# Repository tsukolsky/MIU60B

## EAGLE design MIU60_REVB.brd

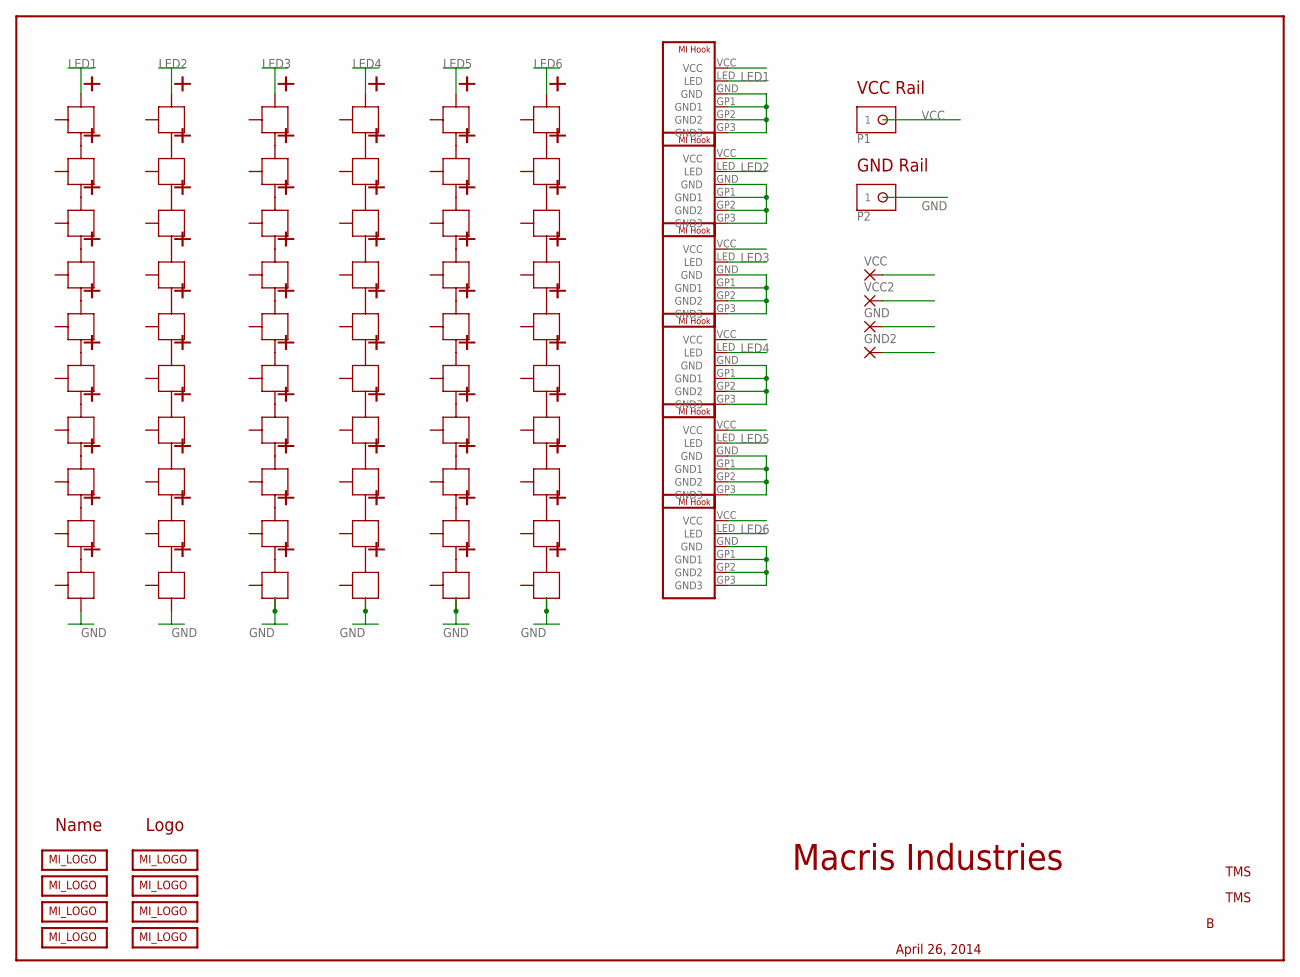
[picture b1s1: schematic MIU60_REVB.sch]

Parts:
GND, GND2: SMD5; SMD2,54-5,08
P1, P2: PAD-10G; PAD_10G
U$1, U$3, U$5, U$6: MI_LOGO-50MIL; MI_LOGO_NAME_2
U$2, U$4, U$7, U$8: MI_LOGO-2014_USA; MACRIS_USA_LOGO
U$9, U$10, U$11, U$12, U$13, U$14: MI_DRIVER_HOOKUP; MI_DRIVE_HOOKUP
U$16, U$17, U$18, U$19, U$20, U$21, U$22, U$23, U$24, U$25, U$26, U$27, U$28, U$29, U$30, U$31, U$32, U$33, U$34, U$35, U$36, U$37, U$38, U$39, U$40, U$41, U$42, U$43, U$44, U$45, U$46, U$47, U$48, U$49, U$50, U$51, U$52, U$53, U$54, U$55, U$56, U$57, U$58, U$59, U$60, U$61, U$62, U$63, U$64, U$65, U$66, U$67, U$68, U$69, U$70, U$71, U$72, U$73, U$74, U$75: CREE_XP; XP
VCC, VCC2: SMD5; SMD2,54-5,08

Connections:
GND: GND.1, GND2.1, P2.1, U$9.GND, U$9.GP1 (GND1), U$9.GP2 (GND2), U$9.GP3 (GND3), U$10.GND, U$10.GP1 (GND1), U$10.GP2 (GND2), U$10.GP3 (GND3), U$11.GND, U$11.GP1 (GND1), U$11.GP2 (GND2), U$11.GP3 (GND3), U$12.GND, U$12.GP1 (GND1), U$12.GP2 (GND2), U$12.GP3 (GND3), U$13.GND, U$13.GP1 (GND1), U$13.GP2 (GND2), U$13.GP3 (GND3), U$14.GND, U$14.GP1 (GND1), U$14.GP2 (GND2), U$14.GP3 (GND3), U$25.NEGATIVE, U$25.NEGATIVE1 (NEGATIVE), U$35.NEGATIVE, U$35.NEGATIVE1 (NEGATIVE), U$45.NEGATIVE, U$45.NEGATIVE1 (NEGATIVE), U$55.NEGATIVE, U$55.NEGATIVE1 (NEGATIVE), U$65.NEGATIVE, U$65.NEGATIVE1 (NEGATIVE), U$75.NEGATIVE, U$75.NEGATIVE1 (NEGATIVE)
LED1: U$9.LED, U$16.POSITIVE, U$16.POSITIVE1 (POSITIVE)
LED2: U$10.LED, U$26.POSITIVE, U$26.POSITIVE1 (POSITIVE)
LED3: U$11.LED, U$36.POSITIVE, U$36.POSITIVE1 (POSITIVE)
LED4: U$12.LED, U$46.POSITIVE, U$46.POSITIVE1 (POSITIVE)
LED5: U$13.LED, U$56.POSITIVE, U$56.POSITIVE1 (POSITIVE)
LED6: U$14.LED, U$66.POSITIVE, U$66.POSITIVE1 (POSITIVE)
unnamed: U$16.NEGATIVE, U$16.NEGATIVE1 (NEGATIVE), U$17.POSITIVE, U$17.POSITIVE1 (POSITIVE)
unnamed: U$17.NEGATIVE, U$17.NEGATIVE1 (NEGATIVE), U$18.POSITIVE, U$18.POSITIVE1 (POSITIVE)
unnamed: U$18.NEGATIVE, U$18.NEGATIVE1 (NEGATIVE), U$19.POSITIVE, U$19.POSITIVE1 (POSITIVE)
unnamed: U$19.NEGATIVE, U$19.NEGATIVE1 (NEGATIVE), U$20.POSITIVE, U$20.POSITIVE1 (POSITIVE)
unnamed: U$20.NEGATIVE, U$20.NEGATIVE1 (NEGATIVE), U$21.POSITIVE, U$21.POSITIVE1 (POSITIVE)
unnamed: U$21.NEGATIVE, U$21.NEGATIVE1 (NEGATIVE), U$22.POSITIVE, U$22.POSITIVE1 (POSITIVE)
unnamed: U$22.NEGATIVE, U$22.NEGATIVE1 (NEGATIVE), U$23.POSITIVE, U$23.POSITIVE1 (POSITIVE)
unnamed: U$23.NEGATIVE, U$23.NEGATIVE1 (NEGATIVE), U$24.POSITIVE, U$24.POSITIVE1 (POSITIVE)
unnamed: U$24.NEGATIVE, U$24.NEGATIVE1 (NEGATIVE), U$25.POSITIVE, U$25.POSITIVE1 (POSITIVE)
unnamed: U$56.NEGATIVE, U$56.NEGATIVE1 (NEGATIVE), U$57.POSITIVE, U$57.POSITIVE1 (POSITIVE)
unnamed: U$57.NEGATIVE, U$57.NEGATIVE1 (NEGATIVE), U$58.POSITIVE, U$58.POSITIVE1 (POSITIVE)
unnamed: U$26.NEGATIVE, U$26.NEGATIVE1 (NEGATIVE), U$27.POSITIVE, U$27.POSITIVE1 (POSITIVE)
unnamed: U$27.NEGATIVE, U$27.NEGATIVE1 (NEGATIVE), U$28.POSITIVE, U$28.POSITIVE1 (POSITIVE)
unnamed: U$28.NEGATIVE, U$28.NEGATIVE1 (NEGATIVE), U$29.POSITIVE, U$29.POSITIVE1 (POSITIVE)
unnamed: U$29.NEGATIVE, U$29.NEGATIVE1 (NEGATIVE), U$30.POSITIVE, U$30.POSITIVE1 (POSITIVE)
unnamed: U$30.NEGATIVE, U$30.NEGATIVE1 (NEGATIVE), U$31.POSITIVE, U$31.POSITIVE1 (POSITIVE)
unnamed: U$32.NEGATIVE, U$32.NEGATIVE1 (NEGATIVE), U$33.POSITIVE, U$33.POSITIVE1 (POSITIVE)
unnamed: U$33.NEGATIVE, U$33.NEGATIVE1 (NEGATIVE), U$34.POSITIVE, U$34.POSITIVE1 (POSITIVE)
unnamed: U$34.NEGATIVE, U$34.NEGATIVE1 (NEGATIVE), U$35.POSITIVE, U$35.POSITIVE1 (POSITIVE)
unnamed: U$31.NEGATIVE, U$31.NEGATIVE1 (NEGATIVE), U$32.POSITIVE, U$32.POSITIVE1 (POSITIVE)
unnamed: U$66.NEGATIVE, U$66.NEGATIVE1 (NEGATIVE), U$67.POSITIVE, U$67.POSITIVE1 (POSITIVE)
unnamed: U$36.NEGATIVE, U$36.NEGATIVE1 (NEGATIVE), U$37.POSITIVE, U$37.POSITIVE1 (POSITIVE)
unnamed: U$37.NEGATIVE, U$37.NEGATIVE1 (NEGATIVE), U$38.POSITIVE, U$38.POSITIVE1 (POSITIVE)
unnamed: U$38.NEGATIVE, U$38.NEGATIVE1 (NEGATIVE), U$39.POSITIVE, U$39.POSITIVE1 (POSITIVE)
unnamed: U$39.NEGATIVE, U$39.NEGATIVE1 (NEGATIVE), U$40.POSITIVE, U$40.POSITIVE1 (POSITIVE)
unnamed: U$40.NEGATIVE, U$40.NEGATIVE1 (NEGATIVE), U$41.POSITIVE, U$41.POSITIVE1 (POSITIVE)
unnamed: U$41.NEGATIVE, U$41.NEGATIVE1 (NEGATIVE), U$42.POSITIVE, U$42.POSITIVE1 (POSITIVE)
unnamed: U$42.NEGATIVE, U$42.NEGATIVE1 (NEGATIVE), U$43.POSITIVE, U$43.POSITIVE1 (POSITIVE)
unnamed: U$43.NEGATIVE, U$43.NEGATIVE1 (NEGATIVE), U$44.POSITIVE, U$44.POSITIVE1 (POSITIVE)
unnamed: U$44.NEGATIVE, U$44.NEGATIVE1 (NEGATIVE), U$45.POSITIVE, U$45.POSITIVE1 (POSITIVE)
unnamed: U$58.NEGATIVE, U$58.NEGATIVE1 (NEGATIVE), U$59.POSITIVE, U$59.POSITIVE1 (POSITIVE)
unnamed: U$59.NEGATIVE, U$59.NEGATIVE1 (NEGATIVE), U$60.POSITIVE, U$60.POSITIVE1 (POSITIVE)
unnamed: U$67.NEGATIVE, U$67.NEGATIVE1 (NEGATIVE), U$68.POSITIVE, U$68.POSITIVE1 (POSITIVE)
unnamed: U$46.NEGATIVE, U$46.NEGATIVE1 (NEGATIVE), U$47.POSITIVE, U$47.POSITIVE1 (POSITIVE)
unnamed: U$47.NEGATIVE, U$47.NEGATIVE1 (NEGATIVE), U$48.POSITIVE, U$48.POSITIVE1 (POSITIVE)
unnamed: U$48.NEGATIVE, U$48.NEGATIVE1 (NEGATIVE), U$49.POSITIVE, U$49.POSITIVE1 (POSITIVE)
unnamed: U$49.NEGATIVE, U$49.NEGATIVE1 (NEGATIVE), U$50.POSITIVE, U$50.POSITIVE1 (POSITIVE)
unnamed: U$50.NEGATIVE, U$50.NEGATIVE1 (NEGATIVE), U$51.POSITIVE, U$51.POSITIVE1 (POSITIVE)
unnamed: U$51.NEGATIVE, U$51.NEGATIVE1 (NEGATIVE), U$52.POSITIVE, U$52.POSITIVE1 (POSITIVE)
unnamed: U$52.NEGATIVE, U$52.NEGATIVE1 (NEGATIVE), U$53.POSITIVE, U$53.POSITIVE1 (POSITIVE)
unnamed: U$53.NEGATIVE, U$53.NEGATIVE1 (NEGATIVE), U$54.POSITIVE, U$54.POSITIVE1 (POSITIVE)
unnamed: U$68.NEGATIVE, U$68.NEGATIVE1 (NEGATIVE), U$69.POSITIVE, U$69.POSITIVE1 (POSITIVE)
unnamed: U$54.NEGATIVE, U$54.NEGATIVE1 (NEGATIVE), U$55.POSITIVE, U$55.POSITIVE1 (POSITIVE)
unnamed: U$60.NEGATIVE, U$60.NEGATIVE1 (NEGATIVE), U$61.POSITIVE, U$61.POSITIVE1 (POSITIVE)
unnamed: U$61.NEGATIVE, U$61.NEGATIVE1 (NEGATIVE), U$62.POSITIVE, U$62.POSITIVE1 (POSITIVE)
unnamed: U$62.NEGATIVE, U$62.NEGATIVE1 (NEGATIVE), U$63.POSITIVE, U$63.POSITIVE1 (POSITIVE)
unnamed: U$63.NEGATIVE, U$63.NEGATIVE1 (NEGATIVE), U$64.POSITIVE, U$64.POSITIVE1 (POSITIVE)
unnamed: U$64.NEGATIVE, U$64.NEGATIVE1 (NEGATIVE), U$65.POSITIVE, U$65.POSITIVE1 (POSITIVE)
unnamed: U$69.NEGATIVE, U$69.NEGATIVE1 (NEGATIVE), U$70.POSITIVE, U$70.POSITIVE1 (POSITIVE)
unnamed: U$70.NEGATIVE, U$70.NEGATIVE1 (NEGATIVE), U$71.POSITIVE, U$71.POSITIVE1 (POSITIVE)
unnamed: U$71.NEGATIVE, U$71.NEGATIVE1 (NEGATIVE), U$72.POSITIVE, U$72.POSITIVE1 (POSITIVE)
unnamed: U$72.NEGATIVE, U$72.NEGATIVE1 (NEGATIVE), U$73.POSITIVE, U$73.POSITIVE1 (POSITIVE)
unnamed: U$73.NEGATIVE, U$73.NEGATIVE1 (NEGATIVE), U$74.POSITIVE, U$74.POSITIVE1 (POSITIVE)
unnamed: U$74.NEGATIVE, U$74.NEGATIVE1 (NEGATIVE), U$75.POSITIVE, U$75.POSITIVE1 (POSITIVE)
VCC: P1.1, U$9.VCC, U$10.VCC, U$11.VCC, U$12.VCC, U$13.VCC, U$14.VCC, VCC.1, VCC2.1

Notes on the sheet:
Macris Industries
TMS
April 26, 2014
VCC Rail
GND Rail
Logo
Name

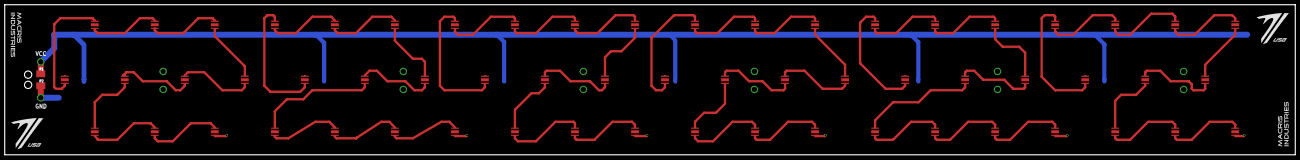
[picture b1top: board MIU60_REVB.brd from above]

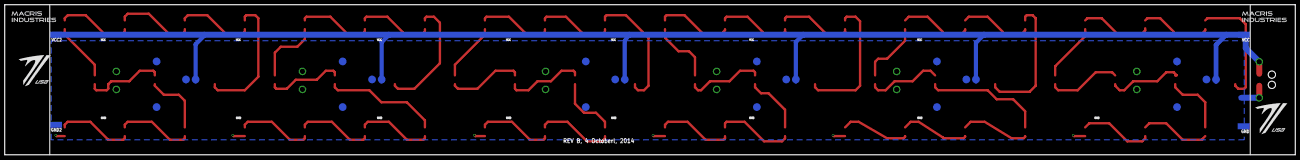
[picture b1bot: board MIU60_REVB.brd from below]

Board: 2 copper layers, 546.1 x 63.5 mm, 80 parts (14 on the bottom side), 62 nets.

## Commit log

2014-10-04 Last rev finished, waiting approval. Added connections to Driver board
2014-12-07 Harrisons updates PLUS changed 4 of the vias to pads int he library file for MI_DRIVE_HOOKUP per request
2014-12-27 Moved some older files
2014-12-27 Harrisons changes that are updated with correct parts for MI Driver Hookup
2014-12-27 Added the final piece in mechanical.lbr for final ground that I for some reason didnt add
2014-12-27 Added folder with harrisons naming conventions
